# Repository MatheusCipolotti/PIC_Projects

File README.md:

# PIC_Projects
Repositório dedicado ao armazenamento de projetos e exemplos de código utilizando os microcontroladores PIC.

# Índice:

- [Potenciômetro Digital DS1267](POT_DIG_DS1267)
- [RTC DS1307](RTC_DS1307)

# Placas:
- [DEV BOARD - 16F877A](DEV_BOARD_16F877A)

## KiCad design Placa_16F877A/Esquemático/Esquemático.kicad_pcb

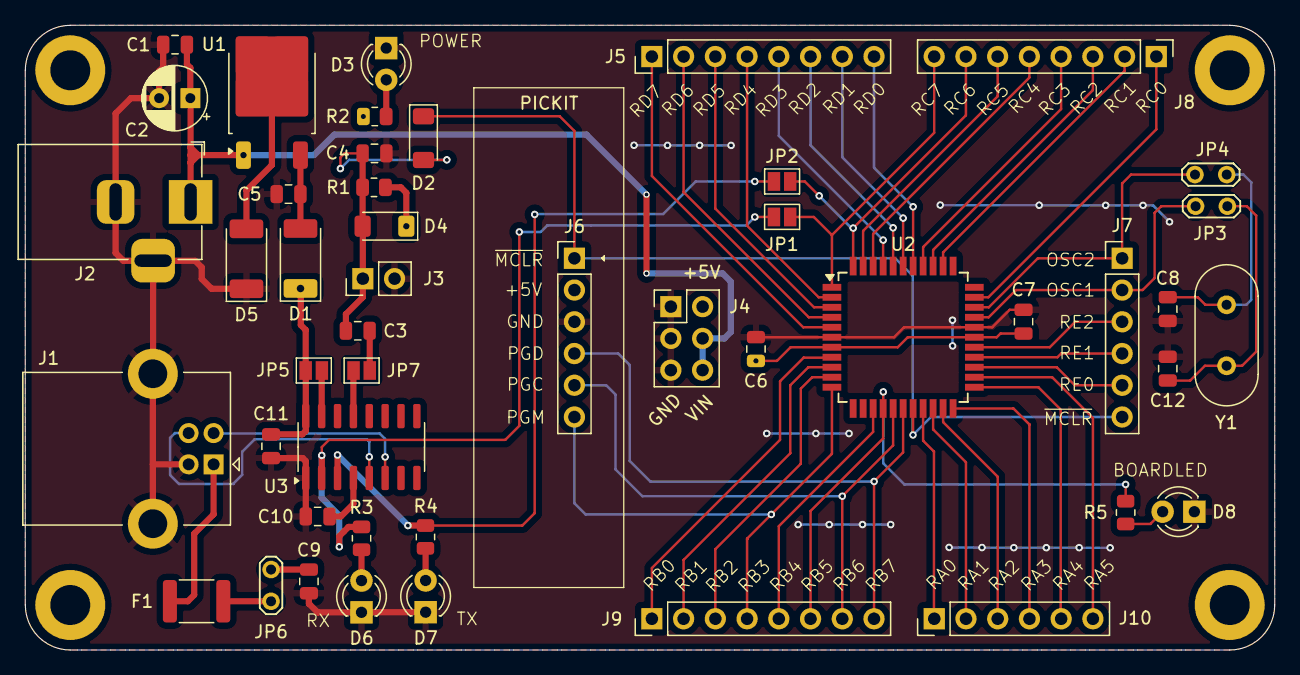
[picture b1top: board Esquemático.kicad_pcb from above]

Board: 2 copper layers, 100.0 x 50.0 mm, 47 parts (0 on the bottom side), 58 nets.

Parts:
C1, C3, C4, C5, C6, C7, C9, C10, C11: 100nF; C_0805_2012Metric
C2: 100uF; CP_Radial_D5.0mm_P2.50mm
C8, C12: 22pF; C_0805_2012Metric
D1, D5: SM4007; D_MELF
D2, D4: LL4148; D_MiniMELF
D3, D6, D7, D8: LED; LED_D3.0mm
F1: MINISMDC110F-2; Fuse_1812_4532Metric
J1: USB_B; USB_B_Lumberg_2411_02_Horizontal
J2: Barrel_Jack_Switch; BarrelJack_Horizontal
J3: Conn_01x02_Pin; PinHeader_1x02_P2.54mm_Vertical
J4: Conn_02x03_Odd_Even; PinHeader_2x03_P2.54mm_Vertical
J5, J8, J9: Conn_01x08_Pin; PinHeader_1x08_P2.54mm_Vertical
J6, J7, J10: Conn_01x06_Pin; PinHeader_1x06_P2.54mm_Vertical
JP1, JP2, JP5, JP7: SolderJumper_2_Open; SolderJumper-2_P1.3mm_Open_Pad1.0x1.5mm
JP3, JP4, JP6: Jumper_2_Open; TestPoint_2Pads_Pitch2.54mm_Drill0.8mm
R1: 1K; R_0805_2012Metric
R2, R3, R4, R5: 2K2; R_0805_2012Metric
U1: LM78M05_TO252; TO-252-2
U2: PIC16F877A-IPT; TQFP-44_10x10mm_P0.8mm
U3: CH340C; SOIC-16_3.9x9.9mm_P1.27mm
Y1: 20MHz; Crystal_HC49-U_Vertical

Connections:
+5V: C6.1, C7.1, C9.1, C11.1, D1.1 (K), D4.1 (K), J4.2, J6.2, JP5.2 (B), JP6.2 (B), R1.2, R2.2, U2.7 (VDD), U2.28 (VDD), U3.16 (VCC)
GND: C1.2, C2.2, C4.2, C5.2, C6.2, C7.2, C8.2, C9.2, C10.1, C11.2, C12.2, D3.1 (K), D5.1 (K), D6.1 (K), D7.1 (K), D8.1 (K), J1.4 (GND), J1.5 (Shield), J2.2, J2.3, J3.2, J4.1, J4.3, J4.5, J6.3, U2.6 (VSS), U2.29 (VSS), U3.1 (GND)
unnamed: C3.2, C4.1, D2.2 (A), D4.2 (A), J3.1, R1.1
unnamed: D5.2 (A), U1.2 (GND)
unnamed: C5.1, D1.2 (A), U1.3 (VO)
unnamed: D3.2 (A), R2.1
unnamed: D8.2 (A), R5.2
unnamed: D6.2 (A), R3.2
unnamed: D7.2 (A), R4.2
unnamed: J1.3 (D+), U3.5 (UD+)
unnamed: J1.2 (D-), U3.6 (UD-)
unnamed: F1.1, JP6.1 (A)
unnamed: C12.1, JP3.2 (B), Y1.1
unnamed: C8.1, JP4.1 (A), Y1.2
unnamed: JP5.1 (A), U3.15 (R232)
unnamed: JP7.1 (A), U3.13 (~DTR)
unnamed: JP1.1 (A), R3.1, U3.2 (TXD)
unnamed: JP2.1 (A), R4.1, U3.3 (RXD)
unnamed: C10.2, U3.4 (V3)
OSC1: J7.2, JP3.1 (A), U2.30 (OSC1/CLKI)
OSC2: J7.1, JP4.2 (B), U2.31 (OSC2/CLKO)
RA0: J10.1, U2.19 (AN0/RA0)
RA1: J10.2, U2.20 (AN1/RA1)
RA2: J10.3, U2.21 (CVref/Vref-/AN2/RA2)
RA3: J10.4, U2.22 (Vref+/AN3/RA3)
RA4: J10.5, U2.23 (C1OUT/T0CKI/RA4)
RA5: J10.6, U2.24 (~SS/C2OUT/AN4/RA5)
RB0: J9.1, U2.8 (INT/RB0)
RB1: J9.2, U2.9 (RB1)
RB2: J9.3, U2.10 (RB2)
RB3: J6.6, J9.4, U2.11 (PGM/RB3)
RB4: J9.5, U2.14 (RB4)
RB5: J9.6, R5.1, U2.15 (RB5)
RB6: J6.5, J9.7, U2.16 (PGC/RB6)
RB7: J6.4, J9.8, U2.17 (PGD/RB7)
RC0: J8.1, U2.32 (T1OSO/T1CKI/RC0)
RC1: J8.2, U2.35 (T1OSI/CCP2/RC1)
RC2: J8.3, U2.36 (CCP1/RC2)
RC3: J8.4, U2.37 (SCK/SCL/RC3)
RC4: J8.5, U2.42 (SDI/SDA/RC4)
RC5: J8.6, U2.43 (SDO/RC5)
RC6: J8.7, JP2.2 (B), U2.44 (CK/TX/RC6)
RC7: J8.8, JP1.2 (B), U2.1 (DT/RX/RC7)
RD0: J5.8, U2.38 (RD0/PSP0)
RD1: J5.7, U2.39 (RD1/PSP1)
RD2: J5.6, U2.40 (RD2/PSP2)
RD3: J5.5, U2.41 (RD3/PSP3)
RD4: J5.4, U2.2 (RD4/PSP4)
RD5: J5.3, U2.3 (RD5/PSP5)
RD6: J5.2, U2.4 (RD6/PSP6)
RD7: J5.1, U2.5 (RD7/PSP7)
RE0: J7.5, U2.25 (RE0/~RD/AN5)
RE1: J7.4, U2.26 (RE1/~WR/AN6)
RE2: J7.3, U2.27 (RE2/~CS/AN7)
RESET: C3.1, JP7.2 (B)
VBUS: F1.2, J1.1 (VBUS)
VDD: C1.1, C2.1, J2.1, J4.4, J4.6, U1.1 (VI)
~MCLR: D2.1 (K), J6.1, J7.6, U2.18 (~MCLR/Vpp)
